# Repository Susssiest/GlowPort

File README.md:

# GlowPort

Web Project Link - https://a360.co/3UtJbmz

Web Project Password - jqk-VNF1dva9ryk*kmr

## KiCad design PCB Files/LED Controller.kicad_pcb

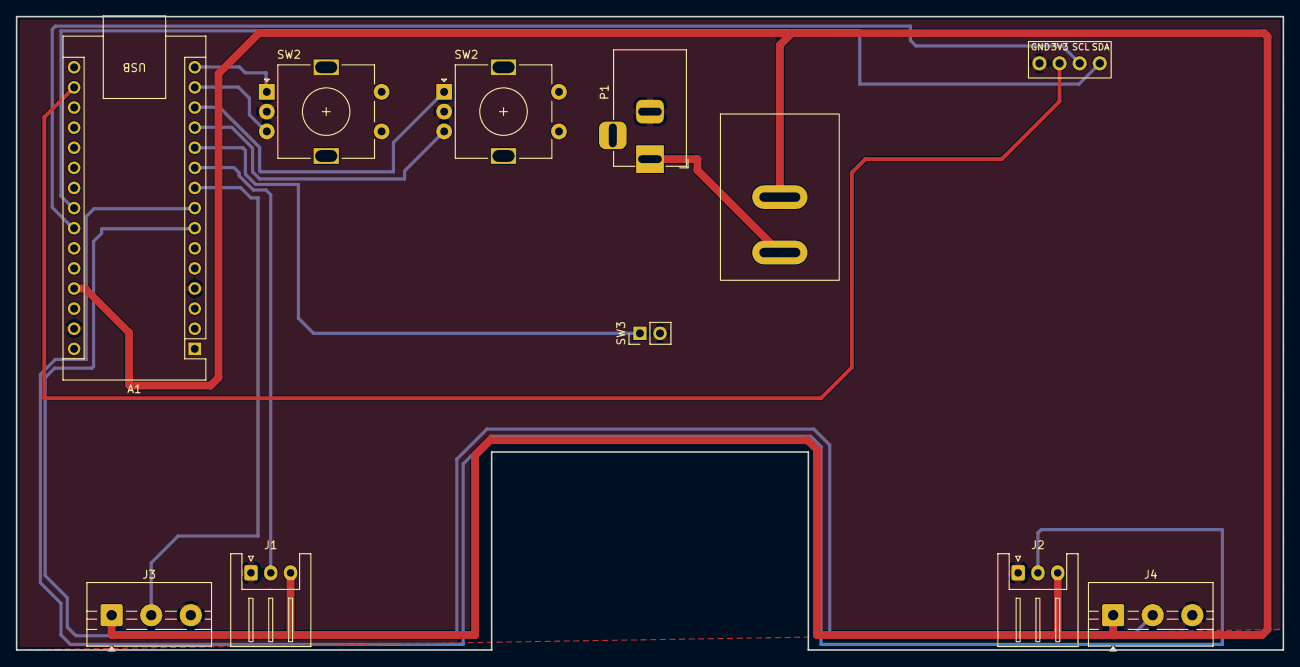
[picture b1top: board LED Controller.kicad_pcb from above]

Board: 2 copper layers, 160.0 x 80.0 mm, 10 parts (0 on the bottom side), 11 nets.

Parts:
A1: Arduino_Nano_v2.x; Arduino_Nano
J1, J2: JST Connector; JST_XH_S3B-XH-A_1x03_P2.50mm_Horizontal
J3, J4: Terminal Block; TerminalBlock_MaiXu_MX126-5.0-03P_1x03_P5.00mm
P1: Barrel_Jack; BarrelJack_Horizontal
SW2, SW2#2: RotaryEncoder: Value; RotaryEncoder_Alps_EC11E-Switch_Vertical_H20mm
SW3: SW_Push; PinHeader_1x02_P2.54mm_Vertical
SW4: SW_SPST; KCD1_THT

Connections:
+5V: A1.27 (+5V), J1.3, J2.3, J3.1, J4.1, P1.1, SW4.1 (A_1)
/D4: A1.7 (D4), J4.2
/D5: A1.8 (D5), J2.2
/D6: A1.9 (D6), J3.2
/D7: A1.10 (D7), J1.2
/D8: A1.11 (D8), SW3.1
/D9: A1.12 (D9), SW2#2.B
/D10: A1.13 (D10), SW2#2.A
/D11: A1.14 (D11), SW2.B
/D12: A1.15 (D12), SW2.A
GND: A1.4 (GND), A1.29 (GND), J1.1, J2.1, J3.3, J4.3, P1.2, SW2.C, SW2#2.C, SW3.2
